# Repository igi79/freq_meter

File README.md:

# freq_meter

PCB for project https://www.elektrolab.eu/blog/presny-meric-frekvence-s-procesorem-atmega8

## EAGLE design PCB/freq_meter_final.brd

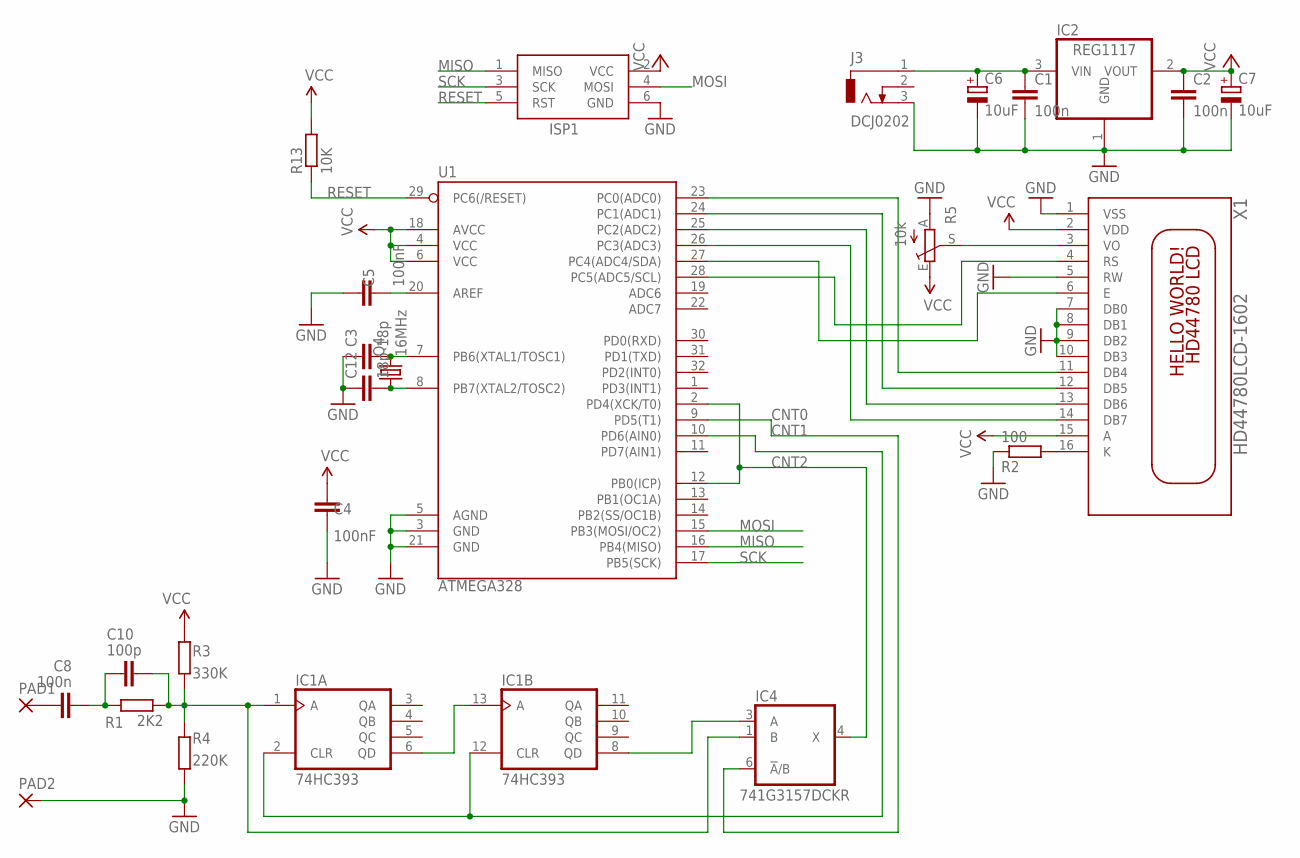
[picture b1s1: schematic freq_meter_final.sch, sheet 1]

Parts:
C1, C2, C8: 100n; C0805
C3, C12: 18p; C0805
C4, C5: 100nF; C0805
C6, C7: 10uF; SMC_E
C10: 100p; C0805
IC1: 74HC393; DIL14
IC2: REG1117; SOT223
IC4: 741G3157DCKR; DCK_R-PDSO-G6
ISP1: AVRISP-6; AVRISP
J3: DCJ0202
PAD1, PAD2: 3,81/1,1
Q4: 16MHz; HC49UP
R1: 2K2; R0805
R2: 100; R0805
R3: 330K; R0805
R4: 220K; R0805
R5: 10k; CA6V
R13: 10K; R0805
U1: ATMEGA328; TQFP32-08
X1: HD44780LCD-1602; LCD1602

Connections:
CNT0: IC4.6 (!A!/B), U1.9 (PD5(T1))
CNT1: IC1.2 (CLR), IC1.12 (CLR), U1.10 (PD6(AIN0))
CNT2: IC4.4 (X), U1.2 (PD4(XCK/T0)), U1.12 (PB0(ICP))
GND: C1.2, C2.2, C3.1, C4.1, C5.2, C6.-, C7.-, C12.1, IC1.7 (GND), IC2.1 (GND), IC4.2 (GND), ISP1.6 (GND), J3.3, PAD2.1, R2.1, R4.2, R5.A, U1.3 (GND), U1.5 (AGND), U1.21 (GND), X1.1 (VSS), X1.5 (RW), X1.7 (DB0), X1.8 (DB1), X1.9 (DB2), X1.10 (DB3)
MISO: ISP1.1 (MISO), U1.16 (PB4(MISO))
MOSI: ISP1.4 (MOSI), U1.15 (PB3(MOSI/OC2))
unnamed: C1.1, C6.+, IC2.3 (VIN), J3.1
unnamed: R5.S, X1.3 (VO)
unnamed: U1.28 (PC5(ADC5/SCL)), X1.4 (RS)
unnamed: U1.26 (PC3(ADC3)), X1.14 (DB7)
unnamed: U1.25 (PC2(ADC2)), X1.13 (DB6)
unnamed: U1.24 (PC1(ADC1)), X1.12 (DB5)
unnamed: U1.23 (PC0(ADC0)), X1.11 (DB4)
unnamed: U1.27 (PC4(ADC4/SDA)), X1.6 (E)
unnamed: C8.1, PAD1.1
unnamed: C10.1, IC1.1 (A), IC4.1 (B), R1.2, R3.1, R4.1
unnamed: R2.2, X1.16 (K)
unnamed: IC1.6 (QD), IC1.13 (A)
unnamed: IC1.8 (QD), IC4.3 (A)
unnamed: C8.2, C10.2, R1.1
unnamed: C3.2, Q4.2, U1.7 (PB6(XTAL1/TOSC1))
unnamed: C12.2, Q4.1, U1.8 (PB7(XTAL2/TOSC2))
unnamed: C5.1, U1.20 (AREF)
RESET: ISP1.5 (RST), R13.1, U1.29 (PC6(/RESET))
SCK: ISP1.3 (SCK), U1.17 (PB5(SCK))
VCC: C2.1, C4.2, C7.+, IC1.14 (VCC), IC2.2 (VOUT), IC4.5 (VCC), ISP1.2 (VCC), R3.2, R5.E, R13.2, U1.4 (VCC), U1.6 (VCC), U1.18 (AVCC), X1.2 (VDD), X1.15 (A)

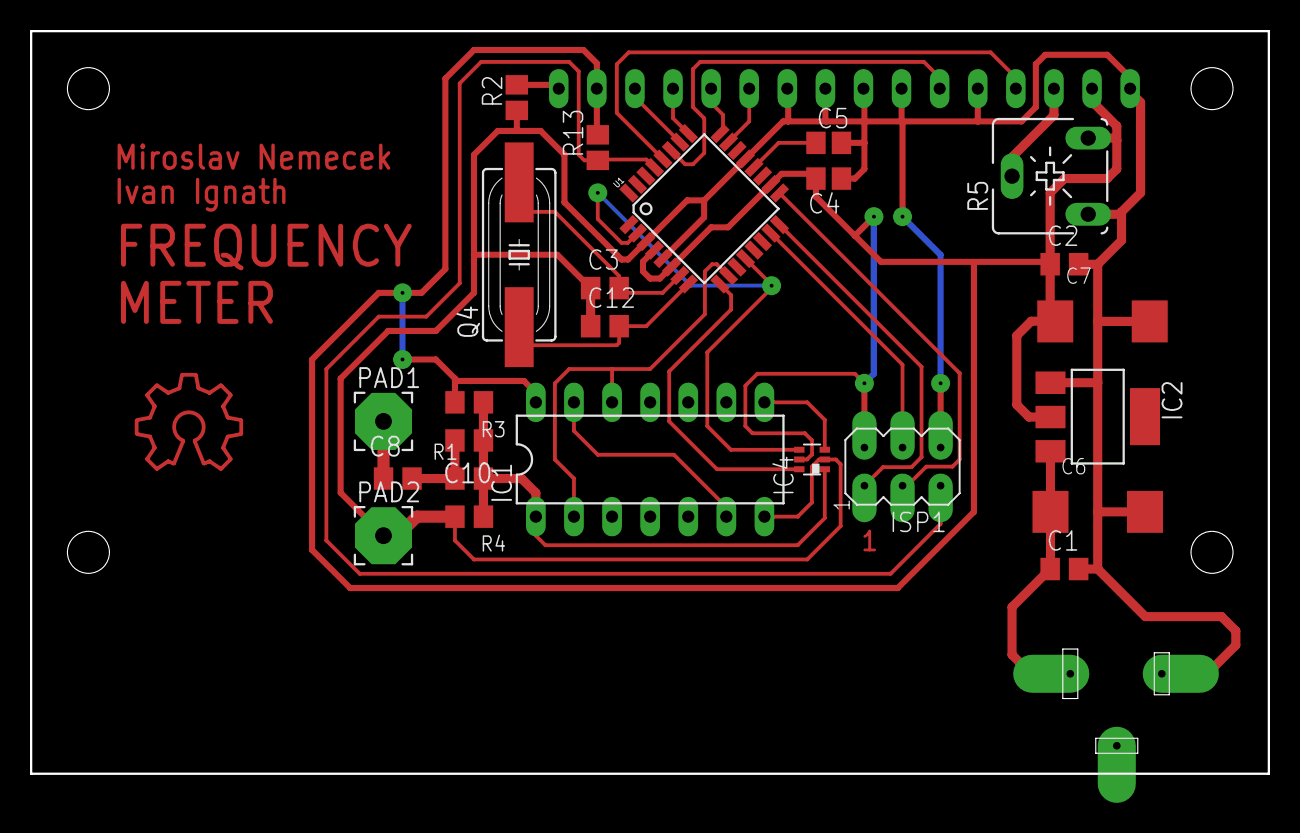
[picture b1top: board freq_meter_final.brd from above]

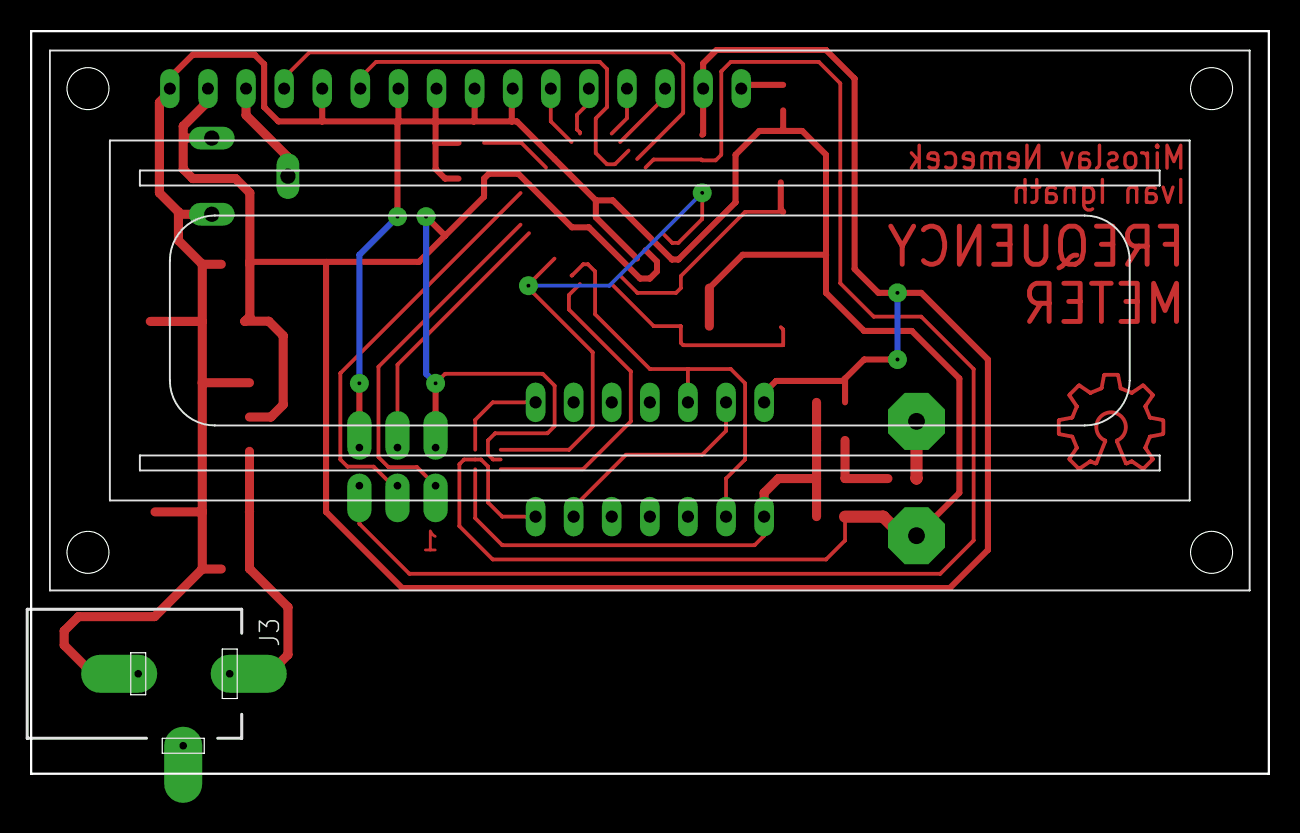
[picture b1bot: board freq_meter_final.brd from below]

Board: 2 copper layers, 82.5 x 49.5 mm, 26 parts (2 on the bottom side), 26 nets.

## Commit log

2021-05-02 init
